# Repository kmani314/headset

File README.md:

# MR Headset

This is an open-source **Mixed Reality** headset that aims to augment the power of human imagination. It aims to do this by using high resolution displays and cameras, as well as a powerful ARM based CPU and GPU. 

Version 0.1 of the mainboard is avaiable in `/hardware/mainboard`, it is designed around an RK3399-based SOM.

[BOM](https://docs.google.com/spreadsheets/d/1svv3ELyh4oFGVD46yAfUMj0UHieJaqO5vQMvadlOVdQ/edit?usp=sharing)

[Digi-Key Shared BOM (Requires account)](https://www.digikey.com/BOM/Create/CreateSharedBom?bomId=8410949)

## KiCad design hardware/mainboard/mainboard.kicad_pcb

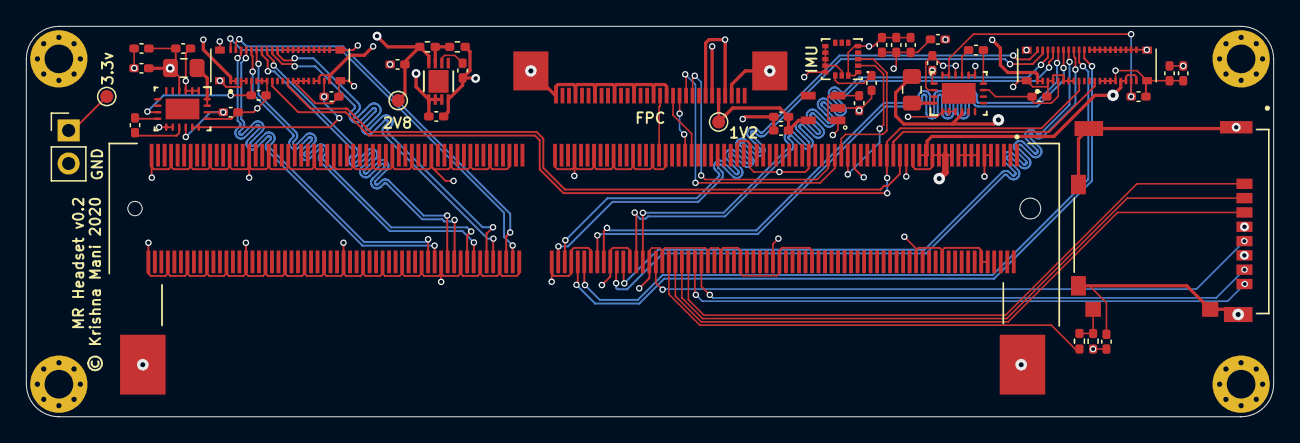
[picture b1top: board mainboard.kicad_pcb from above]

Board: 4 copper layers, 95.8 x 30.0 mm, 49 parts (0 on the bottom side), 69 nets.

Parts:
C1, C2, C4, C5, C11, C18, C19, C21, C22: 4.7uF; C_0402_1005Metric_Pad0.74x0.62mm_HandSolder
C3, C20, C24: 2.2uF; C_0402_1005Metric_Pad0.74x0.62mm_HandSolder
C6, C7, C13: 1uF; C_0402_1005Metric_Pad0.74x0.62mm_HandSolder
C8, C10, C14, C16: 100nF; C_0402_1005Metric_Pad0.74x0.62mm_HandSolder
C9, C15, C17, C25: 10nF; C_0402_1005Metric_Pad0.74x0.62mm_HandSolder
C23, C26: 0.1uF; C_0402_1005Metric_Pad0.74x0.62mm_HandSolder
H1, H2, H3, H4: MountingHole_Pad; MountingHole_2.2mm_M2_Pad_Via
J1: 2309407-1; TE_2309407-1
J2, J6: WP7B-S040VA1-R6000; JAE_WP7B-S040VA1-R6000
J3: Conn_01x02_Male; PinHeader_1x02_P2.54mm_Vertical
J4: 3-84953-0; 68713014522
J5: 503182-1852; MOLEX_503182-1852
L1, L2: 2.2uH; L_0805_2012Metric_Pad1.15x1.40mm_HandSolder
R1: 60k; R_0402_1005Metric_Pad0.72x0.64mm_HandSolder
R2, R4: 10k; R_0402_1005Metric_Pad0.72x0.64mm_HandSolder
R3: 1k; R_0402_1005Metric_Pad0.72x0.64mm_HandSolder
TP1, TP3, TP4: TestPoint; TestPoint_Pad_D1.0mm
U1, U4: TPS65132; TPS65132WRVCT
U2: MIC5504-1.2YM5-TR; SOT23-5P95_280X145XL45X37N
U3: MCP1725-ADJE_MC
U5: ICM-20602; PQFN50P300X300X80-16N

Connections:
+1V2: C7.1, C10.1, J4.5, TP1.1, U2.5
+1V8: C24.2, C25.2, C26.1, J1.29, J1.31, J2.21, J2.23, J2.24, J4.6, J6.21, J6.23, J6.24, U5.1, U5.5, U5.16
+2V8: C8.1, C13.1, J2.39, J2.40, J4.4, J4.7, J6.39, J6.40, R1.1, TP4.1, U3.8
+3V3: C1.1, C6.1, C11.1, C14.1, C15.1, C16.1, C17.1, C18.1, J1.21, J1.23, J1.25, J1.27, J1.33, J1.76, J3.1, J5.4, L1.1, L2.1, R4.2, TP3.1, U1.4, U2.1, U2.3, U3.1, U3.2, U3.3, U4.4
+5V: J1.13, J1.15, J1.17, J1.19
/GPIO2_B3_CIF_CLKOUTA: J1.111, J4.14
/GPIO_BL: J1.41, J2.32, J6.32
/I2C1_SCL: J1.53, U5.2
/I2C1_SDA: J1.55, U5.3
/I2C2_SCL: J1.59, J4.9
/I2C2_SDA: J1.57, J4.10
/LCD 1/AVDD: C5.1, J2.22, U1.15, U1.16
/LCD 1/AVEE: C2.1, J2.36, U1.9
/LCD 2/AVDD: C22.1, J6.22, U4.15, U4.16
/LCD 2/AVEE: C19.1, J6.36, U4.9
/MIPI_CSI0_PWN: J1.101, J4.12
/MIPI_CSI1_RST: J1.103, J4.11
/MIPI_RX0_CLK+: J1.129, J4.25
/MIPI_RX0_CLK-: J1.127, J4.26
/MIPI_RX0_D0+: J1.141, J4.28
/MIPI_RX0_D0-: J1.139, J4.29
/MIPI_RX0_D1+: J1.135, J4.22
/MIPI_RX0_D1-: J1.133, J4.23
/MIPI_RX0_D2+: J1.123, J4.19
/MIPI_RX0_D2-: J1.121, J4.20
/MIPI_RX0_D3+: J1.117, J4.16
/MIPI_RX0_D3-: J1.115, J4.17
/MIPI_TX0_CLK+: J1.162, J2.6
/MIPI_TX0_CLK-: J1.160, J2.5
/MIPI_TX0_D0+: J1.174, J2.4
/MIPI_TX0_D0-: J1.172, J2.3
/MIPI_TX0_D1+: J1.168, J2.8
/MIPI_TX0_D1-: J1.166, J2.7
/MIPI_TX0_D2+: J1.156, J2.10
/MIPI_TX0_D2-: J1.154, J2.9
/MIPI_TX0_D3+: J1.150, J2.2
/MIPI_TX0_D3-: J1.148, J2.1
/MIPI_TX1_CLK+: J1.130, J6.6
/MIPI_TX1_CLK-: J1.128, J6.5
/MIPI_TX1_D0+: J1.118, J6.4
/MIPI_TX1_D0-: J1.116, J6.3
/MIPI_TX1_D1+: J1.124, J6.8
/MIPI_TX1_D1-: J1.122, J6.7
/MIPI_TX1_D2+: J1.136, J6.10
/MIPI_TX1_D2-: J1.134, J6.9
/MIPI_TX1_D3+: J1.142, J6.2
/MIPI_TX1_D3-: J1.140, J6.1
/RESX_0: J1.37, J2.29
/RESX_1: J1.39, J6.29
/SDMMC0_CLK: J1.112, J5.5
/SDMMC0_CMD: J1.106, J5.3
/SDMMC0_D0: J1.98, J5.7
/SDMMC0_D1: J1.100, J5.8
/SDMMC0_D2: J1.102, J5.1
/SDMMC0_D3: J1.104, J5.2
/SDMMC0_DET_L: J1.108, R3.2
GND: C1.2, C2.2, C4.1, C5.2, C6.2, C7.2, C8.2, C9.2, C10.2, C11.2, C13.2, C14.2, C15.2, C16.2, C17.2, C18.2, C19.2, C21.1, C22.2, C23.1, C24.1, C25.1, C26.2, H1.1, H2.1, H3.1, H4.1, J1.9, J1.10, J1.11, J1.12, J1.24, J1.32, J1.35, J1.51, J1.64, J1.65, J1.74, J1.83, J1.86, J1.87, J1.92, J1.96, J1.109, J1.110, J1.113, J1.114, J1.119, J1.120, J1.125, J1.126, J1.131, J1.132, J1.137, J1.138, J1.143, J1.144, J1.146, J1.149, J1.152, J1.155, J1.158, J1.161, J1.164, J1.167, J1.170, J1.173, J1.176, J1.179, J1.182, J1.185, J1.188, J1.191, J1.194, J1.197, J1.200, J1.203, J1.206, J1.209, J1.212, J1.217, J1.218, J1.223, J1.224, J1.229, J1.230, J1.235, J1.236, J1.241, J1.242, J1.247, J1.248, J1.253, J1.254, J1.259, J1.260, J1.SH1, J1.SH2, J2.11, J2.12, J2.13, J2.14, J2.15, J2.16, J2.17, J2.18, J2.19, J2.20, J2.25, J2.26, J2.27, J2.28, J2.33, J2.34, J2.35, J2.37, J2.38, J2.S1, J2.S2, J2.S3, J2.S4, J3.2, J4.3, J4.13, J4.15, J4.18, J4.21, J4.24, J4.27, J4.30, J4.Z1, J4.Z2, J5.6, J5.P1, J5.P2, J5.P3, J5.P4, J5.P5, J5.SW, J6.11, J6.12, J6.13, J6.14, J6.15, J6.16, J6.17, J6.18, J6.19, J6.20, J6.25, J6.26, J6.27, J6.28, J6.33, J6.34, J6.35, J6.37, J6.38, J6.S1, J6.S2, J6.S3, J6.S4, R2.2, U1.1, U1.2, U1.3, U1.11, U1.12, U1.17, U2.2, U3.4, U4.1, U4.2, U4.3, U4.11, U4.12, U4.17, U5.9, U5.10, U5.11, U5.12, U5.13, U5.15
unnamed: C3.1, U1.13
unnamed: C3.2, U1.10
unnamed: C4.2, U1.14, U1.18
unnamed: C9.1, U3.6
unnamed: C20.1, U4.13
unnamed: C20.2, U4.10
unnamed: C21.2, U4.14, U4.18
unnamed: C23.2, U5.14
unnamed: J5.DT, R3.1, R4.1
unnamed: L1.2, U1.19, U1.20
unnamed: L2.2, U4.19, U4.20
unnamed: R1.2, R2.1, U3.7

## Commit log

2020-10-14 Initial commit, rk3399 chosen, initial stuff done in pcb
2020-10-14 README updates
2020-10-18 displays done, sd card and camera is left
2020-10-19 finished camera, sd, imu, power supplies, might be done with schematic
2020-10-19 footprints assigned, ready to begin pcb design
2020-10-24 mipi done, power almost done
2020-10-24 0.1 routing done, will merge after cleaning up silkscreen
2020-10-24 fixed silkscreen
2020-10-24 add fpc
2020-10-25 bugfixes
2020-10-25 add shared bom
2020-10-26 minor fix
2020-10-27 3d models, 1v2 regulator footprint change
2020-11-01 start on v0.2
2020-11-03 only camera mipi left for v0.2
2020-11-21 things
2020-11-27 redesign started, symbol scripts, new dsi chip
2020-11-28 finish sch arch, remove coproc, add bl driver, need to do TC power supply
2020-11-29 finish basic schematic, need to decide audio situation
2020-11-30 cleanup, audio pll, decide board layout

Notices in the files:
hardware/mainboard/mainboard.kicad_pcb:
© Krishna Mani 2020
parts and their libraries:
Copyright 2016 Accelerated Designs. All rights reserved.
